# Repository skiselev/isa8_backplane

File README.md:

# ISA 8-bit Backplane
Compact ISA 8-bit Backplane board

## Introduction
This backplane was designed as a smaller version of [Micro ATX ISA Backplane](https://www.retrobrewcomputers.org/doku.php?id=boards:isa:isa-backplane:start). It can be used to build a compact IBM PC/XT compatible system using the [Micro 8088](https://github.com/skiselev/micro_8088)
processor board, and the 8-bit ISA cards that I've designed:
[ISA Super VGA](http://www.malinov.com/Home/sergeys-projects/isa-supervga),
[ISA Floppy Disk and Serial Controller](http://www.malinov.com/Home/sergeys-projects/isa-fdc-and-uart),
[XT-CF-Lite](http://www.malinov.com/Home/sergeys-projects/xt-cf-lite),
[ISA OPL2](http://www.malinov.com/Home/sergeys-projects/isa-opl2-card).

## Specifications
* 7 ISA 8-bit (62 pin) slots
* ATX power supply connector, and ATX power control circuit
* Bi-color activity LED, that changes the color when the processor is executing the code (the color changes every time A7 address line changes its value)
* The form factor is (mostly) compatible with ATX / Micro ATX
* Pads for optional termination resistors

## Hardware Documentation

### Schematic and PCB Layout

[Schematic - Version 1.0](KiCad/ISA8_Backplane-Schematic-1.0.pdf)

[PCB Layout - Version 1.0](KiCad/ISA8_Backplane-Board-1.0.pdf)

### Building Insturctions

Please refer to [Building Instructions](Building_Instructions.md) page for detailed instructions.

### Jumpers, Connectors, and Switches

#### P1 - ATX power connector
Pin | Description                    | Pin | Description
--- | ------------------------------ | --- | ------------------------------
1   | +3.3V power supply (not used)  | 11  | +3.3V power supply (not used)
2   |	+3.3V power supply (not used)  | 12  | -12V power supply
3   |	GND                            | 13  | Ground
4   |	+5V power supply               | 14  | Power supply ON signal
5   |	Ground                         | 15  | Ground
6   |	+5V power supply               | 16  | Ground
7   | Ground                         | 17  | Ground
8   | Power good (not used)          | 18  | -5V power supply (not used)*
9   | +5V standby power supply       | 19  | +5V power supply
10  | +12V power supply              | 20  | +5V power supply

*Note: -5V is not provided by most ATX power supplies. It is generated using an on board voltage regulator instead*

#### P2 - Power Switch connector
Pin | Description
--- | -----------
1   | Ground
2   |	Power ON signal

#### P3 - Power LED connector
Pin | Description
--- | -----------
1   | LED+
2   |	Ground

#### SW1 - Power Switch
Press SW1 to turn power on or off. The SW1 is connected in parallel with P2

### Bill of Materials - Version 1.0

[ISA 8-bit Backplane project on Mouser.com](https://www.mouser.com/ProjectManager/ProjectDetail.aspx?AccessID=9a09040b52) - View and order all components except of the PCB.

[ISA 8-bit Backplane project on OSH Park](https://oshpark.com/shared_projects/Y8dcyt5m) - View and order the PCB.

Component type     | Reference | Description                       | Quantity | Possible sources and notes 
------------------ | --------- | --------------------------------- | -------- | --------------------------
PCB                |           | ISA 8-bit Backplane PCB - Version 1.0  | 1   | Refer to the [RetroBrew Computers Board Inventory](https://retrobrewcomputers.org/doku.php?id=boardinventory#xi_8088_project_sergey_kiselev) page for ordering information, or order from a PCB manufacturer of your choice using provided Gerber or KiCad files
Integrated Circuit | U1        | 74HCT74, DIP-14 package           | 1        | Mouser [595-SN74AHCT74N](https://www.mouser.com/ProductDetail/595-SN74AHCT74N)
Integrated Circuit | U2        | 74HCT14, DIP-14 package           | 1        | Mouser [595-SN74AHCT14N](https://www.mouser.com/ProductDetail/595-SN74AHCT14N)
Integrated Circuit | U3        | LM7905C -5V voltage regulator     | 1        | Mouser [512-LM7905CT](https://www.mouser.com/ProductDetail/512-LM7905CT)
IC Socket          | U1, U2    | DIP-14, 300 mil socket            | 2        | Mouser [517-4814-3000-CP](https://www.mouser.com/ProductDetail/517-4814-3000-CP)
LED                | D1        | 3 mm, blue LED indicator          | 1        | Mouser [696-SSL-LX3054USBD](https://www.mouser.com/ProductDetail/696-SSL-LX3054USBD)
LED                | D2        | 3 mm, bi-color red/green LED indicator | 1   | Mouser [696-SSL-LX3054IGW](https://www.mouser.com/ProductDetail/696-SSL-LX3054IGW)
Diode              | D3, D4    | 1N4148                            | 2        | Mouser [512-1N4148](https://www.mouser.com/ProductDetail/512-1N4148)
Tactile Button     | SW1       | 6 mm tactile button, straight     | 1        | Mouser [653-B3F-1000](https://www.mouser.com/ProductDetail/653-B3F-1000)
Connector          | P1        | 20 pin ATX power connector        | 1        | Mouser [538-46015-2006](https://www.mouser.com/ProductDetail/538-46015-2006)
Connector          | P2, P3    | 4 pin header, 2.54 mm pitch       | 2        | Mouser [649-68002-104HLF](https://www.mouser.com/ProductDetail/649-68002-104HLF)
Connector          | BUS1-BUS7 | 62 pin card edge connector, 2.54 mm pitch | 7 | Mouser [571-6-5530843-5](https://www.mouser.com/ProductDetail/571-6-5530843-5)
Capacitor          | C1 - C19  | 10 uF, 16V, MLCC, 5 mm lead spacing    | 19       | Mouser [810-FG28X5R1E106MR06](https://www.mouser.com/ProductDetail/810-FG28X5R1E106MR06)
Capacitor          | C20       | 1 uF, MLCC, 5 mm lead spacing     | 1        | Mouser [810-FG28X5R1H105KRT0](https://www.mouser.com/ProductDetail/810-FG28X5R1H105KRT0)
Capacitor          | C21, C22  | 0.1 uF, MLCC, 5 mm lead spacing   | 2        | Mouser [594-K104K15X7RF53H5](https://www.mouser.com/ProductDetail/594-K104K15X7RF53H5)
Resistor           | R1, R2    | 10 kohm, through hole             | 2        | Mouser [291-10K-RC](https://www.mouser.com/ProductDetail/291-10K-RC)
Resistor           | R3        | 1 kohm, through hole              | 1        | Mouser [291-1K-RC](https://www.mouser.com/ProductDetail/291-1K-RC)
Resistor           | R4 - R7   | 470 ohm, through hole             | 4        | Mouser [291-470-RC](https://www.mouser.com/ProductDetail/291-470-RC)
Resistor Array     | RR1 - RR5 | do not populate                   |          | Optional, should not be populated

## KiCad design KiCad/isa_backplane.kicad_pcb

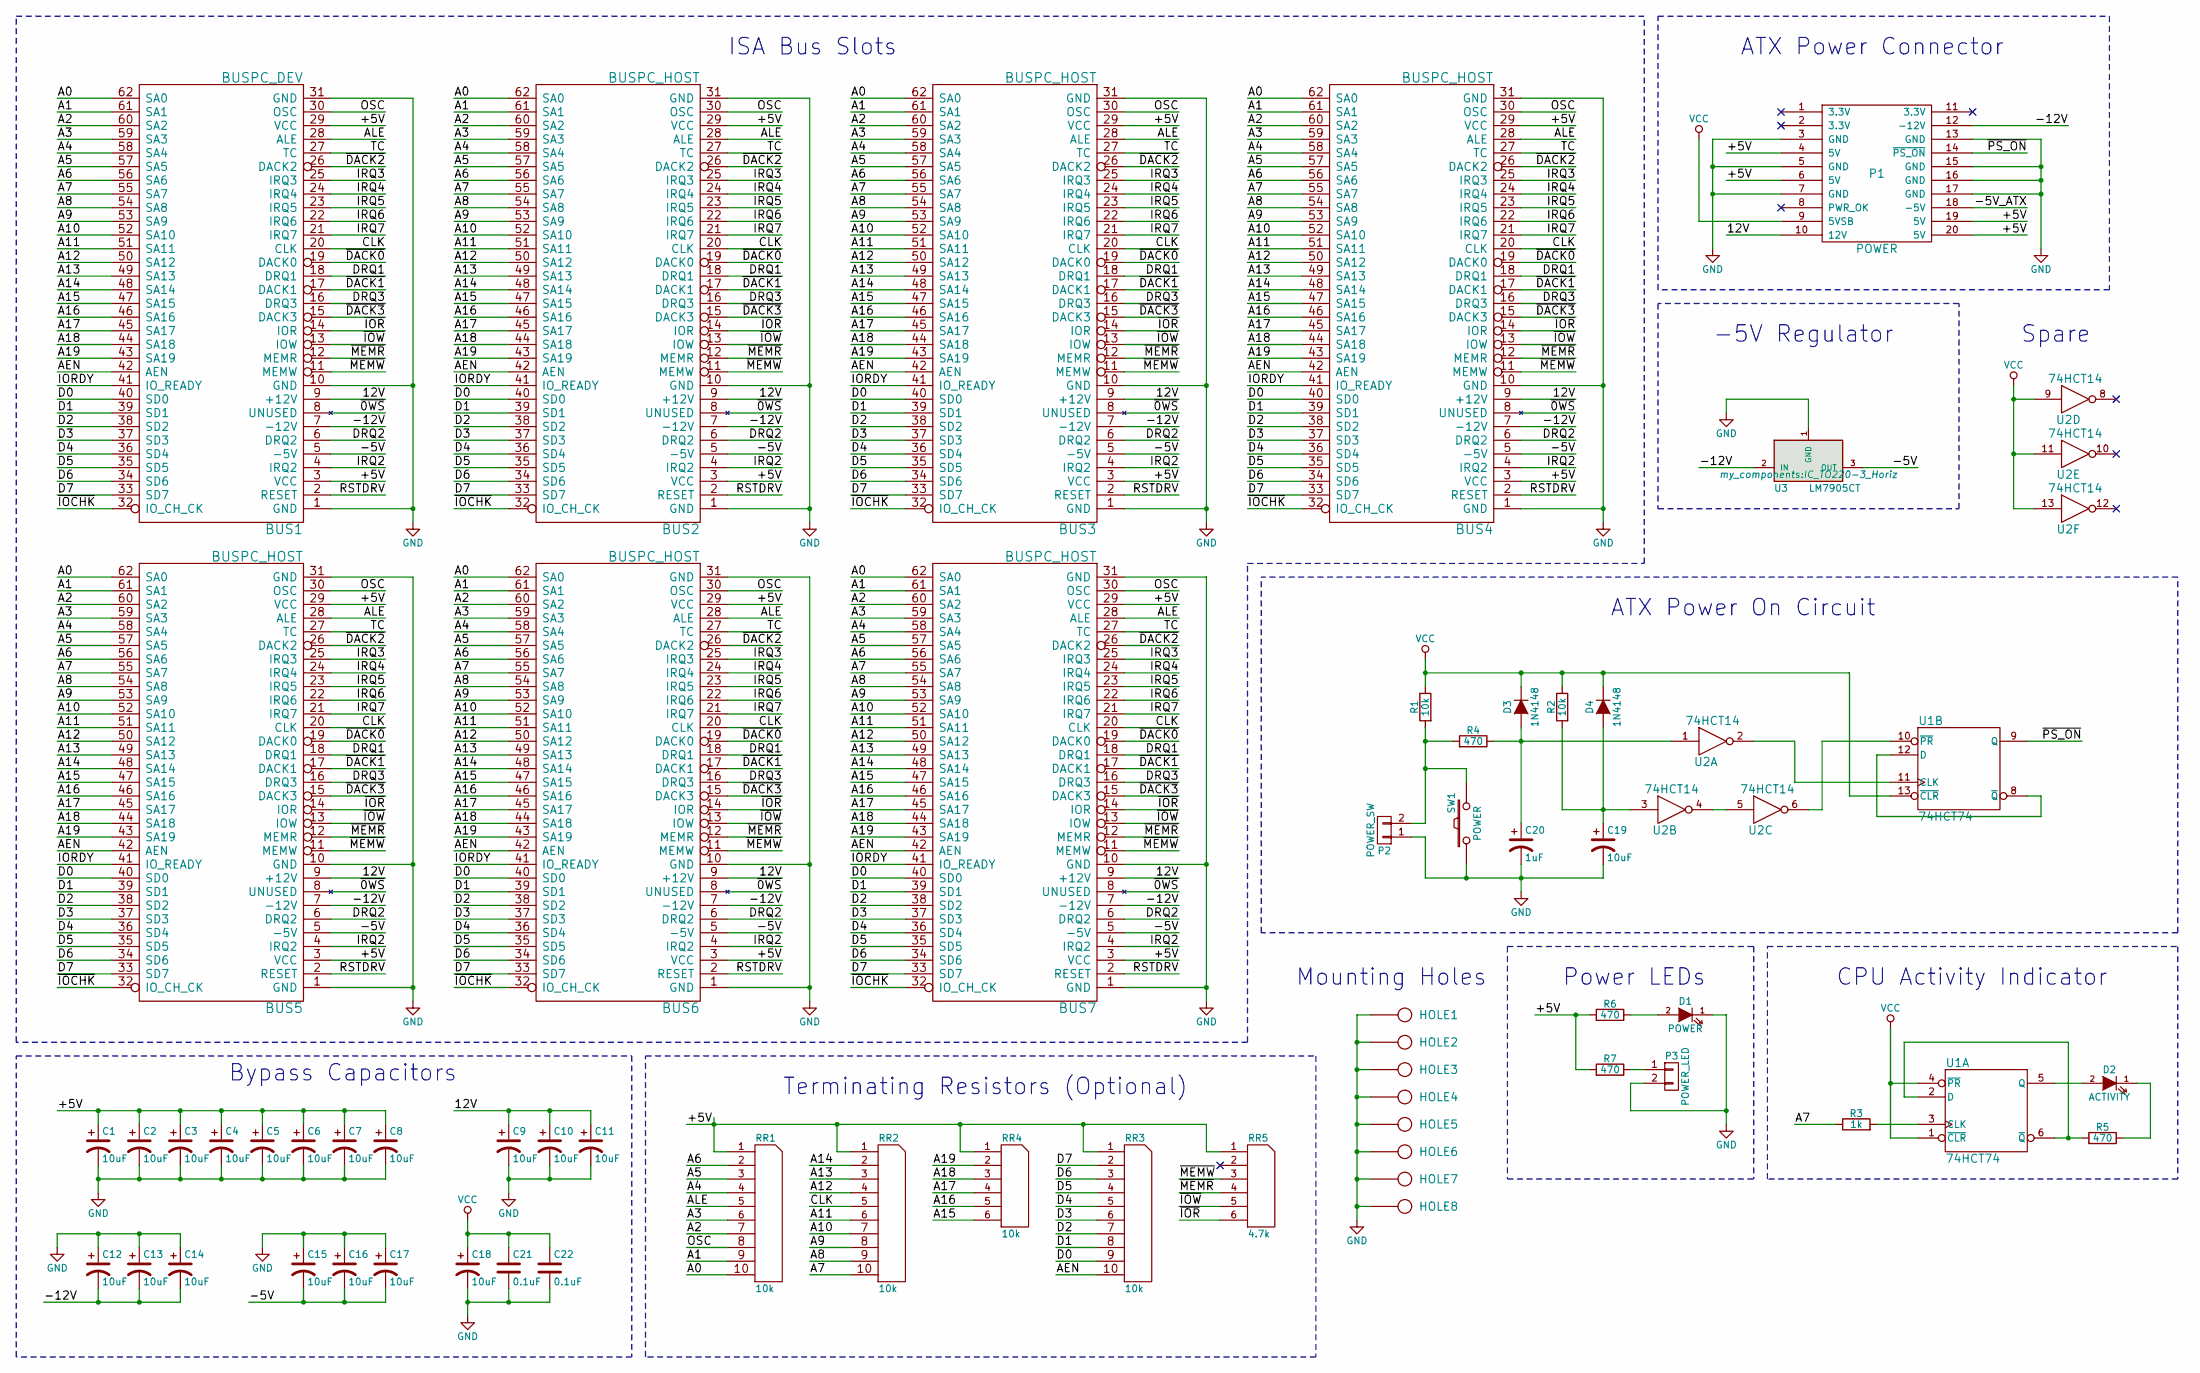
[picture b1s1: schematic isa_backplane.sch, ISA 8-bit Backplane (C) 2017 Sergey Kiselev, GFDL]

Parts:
BUS1: BUSPC_DEV; Conn_Edge_ISA8
BUS2, BUS3, BUS4, BUS5, BUS6, BUS7: BUSPC_HOST; Conn_Edge_ISA8
C1, C2, C3, C4, C5, C6, C7, C8, C9, C10, C11, C12, C13, C14, C15, C16, C17, C18, C19: 10uF; Cap_Tant_508
C20: 1uF; Cap_Tant_508
C21, C22: 0.1uF; Cap_Cer_508
D1: POWER; LED_3mm
D2: ACTIVITY; LED_3mm
D3, D4: 1N4148; Diode_762
HOLE1, HOLE2, HOLE3, HOLE4, HOLE5, HOLE6, HOLE7, HOLE8: HOLE; Hole_4mm
P1: POWER; Conn_Power_ATX_20pin
P2: POWER_SW; Conn_Pin_Header_2x1_2.54mm
P3: POWER_LED; Conn_Pin_Header_2x1_2.54mm
R1, R2: 10k; Res_762
R3: 1k; Res_762
R4, R5, R6, R7: 470; Res_762
RR1, RR2, RR3: 10k; Conn_SIL10
RR4: 10k; Conn_SIL6
RR5: 4.7k; Conn_SIL6
SW1: POWER; Switch_Tactile_6mm
U1: 74HCT74; IC_DIP14_300
U2: 74HCT14; IC_DIP14_300
U3: LM7905CT; IC_TO220-3_Horiz

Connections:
/12V: BUS1.9 (+12V), BUS2.9 (+12V), BUS3.9 (+12V), BUS4.9 (+12V), BUS5.9 (+12V), BUS6.9 (+12V), BUS7.9 (+12V), C9.1, C10.1, C11.1, P1.10 (12V)
/+5V: BUS1.3 (VCC), BUS1.29 (VCC), BUS2.3 (VCC), BUS2.29 (VCC), BUS3.3 (VCC), BUS3.29 (VCC), BUS4.3 (VCC), BUS4.29 (VCC), BUS5.3 (VCC), BUS5.29 (VCC), BUS6.3 (VCC), BUS6.29 (VCC), BUS7.3 (VCC), BUS7.29 (VCC), C1.1, C2.1, C3.1, C4.1, C5.1, C6.1, C7.1, C8.1, P1.4 (5V), P1.6 (5V), P1.19 (5V), P1.20 (5V), R6.2, R7.2, RR1.1 (COM), RR2.1 (COM), RR3.1 (COM), RR4.1 (COM), RR5.1 (COM)
/-5V: BUS1.5 (-5V), BUS2.5 (-5V), BUS3.5 (-5V), BUS4.5 (-5V), BUS5.5 (-5V), BUS6.5 (-5V), BUS7.5 (-5V), C15.2, C16.2, C17.2, U3.3 (OUT)
/-5V_ATX: P1.18 (-5V)
/-12V: BUS1.7 (-12V), BUS2.7 (-12V), BUS3.7 (-12V), BUS4.7 (-12V), BUS5.7 (-12V), BUS6.7 (-12V), BUS7.7 (-12V), C12.2, C13.2, C14.2, P1.12 (-12V), U3.2 (IN)
/A0: BUS1.62 (SA0), BUS2.62 (SA0), BUS3.62 (SA0), BUS4.62 (SA0), BUS5.62 (SA0), BUS6.62 (SA0), BUS7.62 (SA0), RR1.10
/A1: BUS1.61 (SA1), BUS2.61 (SA1), BUS3.61 (SA1), BUS4.61 (SA1), BUS5.61 (SA1), BUS6.61 (SA1), BUS7.61 (SA1), RR1.9
/A2: BUS1.60 (SA2), BUS2.60 (SA2), BUS3.60 (SA2), BUS4.60 (SA2), BUS5.60 (SA2), BUS6.60 (SA2), BUS7.60 (SA2), RR1.7
/A3: BUS1.59 (SA3), BUS2.59 (SA3), BUS3.59 (SA3), BUS4.59 (SA3), BUS5.59 (SA3), BUS6.59 (SA3), BUS7.59 (SA3), RR1.6
/A4: BUS1.58 (SA4), BUS2.58 (SA4), BUS3.58 (SA4), BUS4.58 (SA4), BUS5.58 (SA4), BUS6.58 (SA4), BUS7.58 (SA4), RR1.4
/A5: BUS1.57 (SA5), BUS2.57 (SA5), BUS3.57 (SA5), BUS4.57 (SA5), BUS5.57 (SA5), BUS6.57 (SA5), BUS7.57 (SA5), RR1.3
/A6: BUS1.56 (SA6), BUS2.56 (SA6), BUS3.56 (SA6), BUS4.56 (SA6), BUS5.56 (SA6), BUS6.56 (SA6), BUS7.56 (SA6), RR1.2
/A7: BUS1.55 (SA7), BUS2.55 (SA7), BUS3.55 (SA7), BUS4.55 (SA7), BUS5.55 (SA7), BUS6.55 (SA7), BUS7.55 (SA7), R3.1, RR2.10
/A8: BUS1.54 (SA8), BUS2.54 (SA8), BUS3.54 (SA8), BUS4.54 (SA8), BUS5.54 (SA8), BUS6.54 (SA8), BUS7.54 (SA8), RR2.9
/A9: BUS1.53 (SA9), BUS2.53 (SA9), BUS3.53 (SA9), BUS4.53 (SA9), BUS5.53 (SA9), BUS6.53 (SA9), BUS7.53 (SA9), RR2.8
/A10: BUS1.52 (SA10), BUS2.52 (SA10), BUS3.52 (SA10), BUS4.52 (SA10), BUS5.52 (SA10), BUS6.52 (SA10), BUS7.52 (SA10), RR2.7
/A11: BUS1.51 (SA11), BUS2.51 (SA11), BUS3.51 (SA11), BUS4.51 (SA11), BUS5.51 (SA11), BUS6.51 (SA11), BUS7.51 (SA11), RR2.6
/A12: BUS1.50 (SA12), BUS2.50 (SA12), BUS3.50 (SA12), BUS4.50 (SA12), BUS5.50 (SA12), BUS6.50 (SA12), BUS7.50 (SA12), RR2.4
/A13: BUS1.49 (SA13), BUS2.49 (SA13), BUS3.49 (SA13), BUS4.49 (SA13), BUS5.49 (SA13), BUS6.49 (SA13), BUS7.49 (SA13), RR2.3
/A14: BUS1.48 (SA14), BUS2.48 (SA14), BUS3.48 (SA14), BUS4.48 (SA14), BUS5.48 (SA14), BUS6.48 (SA14), BUS7.48 (SA14), RR2.2
/A15: BUS1.47 (SA15), BUS2.47 (SA15), BUS3.47 (SA15), BUS4.47 (SA15), BUS5.47 (SA15), BUS6.47 (SA15), BUS7.47 (SA15), RR4.6
/A16: BUS1.46 (SA16), BUS2.46 (SA16), BUS3.46 (SA16), BUS4.46 (SA16), BUS5.46 (SA16), BUS6.46 (SA16), BUS7.46 (SA16), RR4.5
/A17: BUS1.45 (SA17), BUS2.45 (SA17), BUS3.45 (SA17), BUS4.45 (SA17), BUS5.45 (SA17), BUS6.45 (SA17), BUS7.45 (SA17), RR4.4
/A18: BUS1.44 (SA18), BUS2.44 (SA18), BUS3.44 (SA18), BUS4.44 (SA18), BUS5.44 (SA18), BUS6.44 (SA18), BUS7.44 (SA18), RR4.3
/A19: BUS1.43 (SA19), BUS2.43 (SA19), BUS3.43 (SA19), BUS4.43 (SA19), BUS5.43 (SA19), BUS6.43 (SA19), BUS7.43 (SA19), RR4.2
/AEN: BUS1.42 (AEN), BUS2.42 (AEN), BUS3.42 (AEN), BUS4.42 (AEN), BUS5.42 (AEN), BUS6.42 (AEN), BUS7.42 (AEN), RR3.10
/ALE: BUS1.28 (ALE), BUS2.28 (ALE), BUS3.28 (ALE), BUS4.28 (ALE), BUS5.28 (ALE), BUS6.28 (ALE), BUS7.28 (ALE), RR1.5
/CLK: BUS1.20 (CLK), BUS2.20 (CLK), BUS3.20 (CLK), BUS4.20 (CLK), BUS5.20 (CLK), BUS6.20 (CLK), BUS7.20 (CLK), RR2.5
/D0: BUS1.40 (SD0), BUS2.40 (SD0), BUS3.40 (SD0), BUS4.40 (SD0), BUS5.40 (SD0), BUS6.40 (SD0), BUS7.40 (SD0), RR3.9
/D1: BUS1.39 (SD1), BUS2.39 (SD1), BUS3.39 (SD1), BUS4.39 (SD1), BUS5.39 (SD1), BUS6.39 (SD1), BUS7.39 (SD1), RR3.8
/D2: BUS1.38 (SD2), BUS2.38 (SD2), BUS3.38 (SD2), BUS4.38 (SD2), BUS5.38 (SD2), BUS6.38 (SD2), BUS7.38 (SD2), RR3.7
/D3: BUS1.37 (SD3), BUS2.37 (SD3), BUS3.37 (SD3), BUS4.37 (SD3), BUS5.37 (SD3), BUS6.37 (SD3), BUS7.37 (SD3), RR3.6
/D4: BUS1.36 (SD4), BUS2.36 (SD4), BUS3.36 (SD4), BUS4.36 (SD4), BUS5.36 (SD4), BUS6.36 (SD4), BUS7.36 (SD4), RR3.5
/D5: BUS1.35 (SD5), BUS2.35 (SD5), BUS3.35 (SD5), BUS4.35 (SD5), BUS5.35 (SD5), BUS6.35 (SD5), BUS7.35 (SD5), RR3.4
/D6: BUS1.34 (SD6), BUS2.34 (SD6), BUS3.34 (SD6), BUS4.34 (SD6), BUS5.34 (SD6), BUS6.34 (SD6), BUS7.34 (SD6), RR3.3
/D7: BUS1.33 (SD7), BUS2.33 (SD7), BUS3.33 (SD7), BUS4.33 (SD7), BUS5.33 (SD7), BUS6.33 (SD7), BUS7.33 (SD7), RR3.2
/DRQ1: BUS1.18 (DRQ1), BUS2.18 (DRQ1), BUS3.18 (DRQ1), BUS4.18 (DRQ1), BUS5.18 (DRQ1), BUS6.18 (DRQ1), BUS7.18 (DRQ1)
/DRQ2: BUS1.6 (DRQ2), BUS2.6 (DRQ2), BUS3.6 (DRQ2), BUS4.6 (DRQ2), BUS5.6 (DRQ2), BUS6.6 (DRQ2), BUS7.6 (DRQ2)
/DRQ3: BUS1.16 (DRQ3), BUS2.16 (DRQ3), BUS3.16 (DRQ3), BUS4.16 (DRQ3), BUS5.16 (DRQ3), BUS6.16 (DRQ3), BUS7.16 (DRQ3)
/IORDY: BUS1.41 (IO_READY), BUS2.41 (IO_READY), BUS3.41 (IO_READY), BUS4.41 (IO_READY), BUS5.41 (IO_READY), BUS6.41 (IO_READY), BUS7.41 (IO_READY)
/IRQ2: BUS1.4 (IRQ2), BUS2.4 (IRQ2), BUS3.4 (IRQ2), BUS4.4 (IRQ2), BUS5.4 (IRQ2), BUS6.4 (IRQ2), BUS7.4 (IRQ2)
/IRQ3: BUS1.25 (IRQ3), BUS2.25 (IRQ3), BUS3.25 (IRQ3), BUS4.25 (IRQ3), BUS5.25 (IRQ3), BUS6.25 (IRQ3), BUS7.25 (IRQ3)
/IRQ4: BUS1.24 (IRQ4), BUS2.24 (IRQ4), BUS3.24 (IRQ4), BUS4.24 (IRQ4), BUS5.24 (IRQ4), BUS6.24 (IRQ4), BUS7.24 (IRQ4)
/IRQ5: BUS1.23 (IRQ5), BUS2.23 (IRQ5), BUS3.23 (IRQ5), BUS4.23 (IRQ5), BUS5.23 (IRQ5), BUS6.23 (IRQ5), BUS7.23 (IRQ5)
/IRQ6: BUS1.22 (IRQ6), BUS2.22 (IRQ6), BUS3.22 (IRQ6), BUS4.22 (IRQ6), BUS5.22 (IRQ6), BUS6.22 (IRQ6), BUS7.22 (IRQ6)
/IRQ7: BUS1.21 (IRQ7), BUS2.21 (IRQ7), BUS3.21 (IRQ7), BUS4.21 (IRQ7), BUS5.21 (IRQ7), BUS6.21 (IRQ7), BUS7.21 (IRQ7)
/OSC: BUS1.30 (OSC), BUS2.30 (OSC), BUS3.30 (OSC), BUS4.30 (OSC), BUS5.30 (OSC), BUS6.30 (OSC), BUS7.30 (OSC), RR1.8
/RSTDRV: BUS1.2 (RESET), BUS2.2 (RESET), BUS3.2 (RESET), BUS4.2 (RESET), BUS5.2 (RESET), BUS6.2 (RESET), BUS7.2 (RESET)
/TC: BUS1.27 (TC), BUS2.27 (TC), BUS3.27 (TC), BUS4.27 (TC), BUS5.27 (TC), BUS6.27 (TC), BUS7.27 (TC)
/~0WS: BUS1.8 (UNUSED), BUS2.8 (UNUSED), BUS3.8 (UNUSED), BUS4.8 (UNUSED), BUS5.8 (UNUSED), BUS6.8 (UNUSED), BUS7.8 (UNUSED)
/~DACK0: BUS1.19 (DACK0), BUS2.19 (DACK0), BUS3.19 (DACK0), BUS4.19 (DACK0), BUS5.19 (DACK0), BUS6.19 (DACK0), BUS7.19 (DACK0)
/~DACK1: BUS1.17 (DACK1), BUS2.17 (DACK1), BUS3.17 (DACK1), BUS4.17 (DACK1), BUS5.17 (DACK1), BUS6.17 (DACK1), BUS7.17 (DACK1)
/~DACK2: BUS1.26 (DACK2), BUS2.26 (DACK2), BUS3.26 (DACK2), BUS4.26 (DACK2), BUS5.26 (DACK2), BUS6.26 (DACK2), BUS7.26 (DACK2)
/~DACK3: BUS1.15 (DACK3), BUS2.15 (DACK3), BUS3.15 (DACK3), BUS4.15 (DACK3), BUS5.15 (DACK3), BUS6.15 (DACK3), BUS7.15 (DACK3)
/~IOCHK: BUS1.32 (IO_CH_CK), BUS2.32 (IO_CH_CK), BUS3.32 (IO_CH_CK), BUS4.32 (IO_CH_CK), BUS5.32 (IO_CH_CK), BUS6.32 (IO_CH_CK), BUS7.32 (IO_CH_CK)
/~IOR: BUS1.14 (IOR), BUS2.14 (IOR), BUS3.14 (IOR), BUS4.14 (IOR), BUS5.14 (IOR), BUS6.14 (IOR), BUS7.14 (IOR), RR5.6
/~IOW: BUS1.13 (IOW), BUS2.13 (IOW), BUS3.13 (IOW), BUS4.13 (IOW), BUS5.13 (IOW), BUS6.13 (IOW), BUS7.13 (IOW), RR5.5
/~MEMR: BUS1.12 (MEMR), BUS2.12 (MEMR), BUS3.12 (MEMR), BUS4.12 (MEMR), BUS5.12 (MEMR), BUS6.12 (MEMR), BUS7.12 (MEMR), RR5.4
/~MEMW: BUS1.11 (MEMW), BUS2.11 (MEMW), BUS3.11 (MEMW), BUS4.11 (MEMW), BUS5.11 (MEMW), BUS6.11 (MEMW), BUS7.11 (MEMW), RR5.3
/~PS_ON: P1.14 (~PS_ON), U1.9 (Q)
GND: BUS1.1 (GND), BUS1.10 (GND), BUS1.31 (GND), BUS2.1 (GND), BUS2.10 (GND), BUS2.31 (GND), BUS3.1 (GND), BUS3.10 (GND), BUS3.31 (GND), BUS4.1 (GND), BUS4.10 (GND), BUS4.31 (GND), BUS5.1 (GND), BUS5.10 (GND), BUS5.31 (GND), BUS6.1 (GND), BUS6.10 (GND), BUS6.31 (GND), BUS7.1 (GND), BUS7.10 (GND), BUS7.31 (GND), C1.2, C2.2, C3.2, C4.2, C5.2, C6.2, C7.2, C8.2, C9.2, C10.2, C11.2, C12.1, C13.1, C14.1, C15.1, C16.1, C17.1, C18.2, C19.2, C20.2, C21.2, C22.2, D1.1 (K), HOLE1.1, HOLE2.1, HOLE3.1, HOLE4.1, HOLE5.1, HOLE6.1, HOLE7.1, HOLE8.1, P1.3 (GND), P1.5 (GND), P1.7 (GND), P1.13 (GND), P1.15 (GND), P1.16 (GND), P1.17 (GND), P2.1, P3.2, SW1.1, U1.7 (GND), U2.7 (GND), U3.1 (GND)
unnamed: C19.1, D4.2 (A), R2.2, U2.3
unnamed: C20.1, D3.2 (A), R4.1, U2.1
unnamed: D1.2 (A), R6.1
unnamed: D2.1 (K), R5.1
unnamed: D2.2 (A), U1.5 (Q)
unnamed: P2.2, R1.2, R4.2, SW1.2
unnamed: P3.1, R7.1
unnamed: R3.2, U1.3 (CLK)
unnamed: R5.2, U1.2 (D), U1.6 (~Q)
unnamed: U1.10 (~PR), U2.6
unnamed: U1.11 (CLK), U2.2
unnamed: U1.8 (~Q), U1.12 (D)
unnamed: U2.4, U2.5
VCC: C18.1, C21.1, C22.1, D3.1 (K), D4.1 (K), P1.9 (5VSB), R1.1, R2.1, U1.1 (~CLR), U1.4 (~PR), U1.13 (~CLR), U1.14 (VCC), U2.9, U2.11, U2.13, U2.14 (VCC)

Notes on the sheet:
Power LEDs
-5V Regulator
CPU Activity Indicator
ATX Power Connector
Mounting Holes
ATX Power On Circuit
Bypass Capacitors
ISA Bus Slots
Terminating Resistors (Optional)
Spare

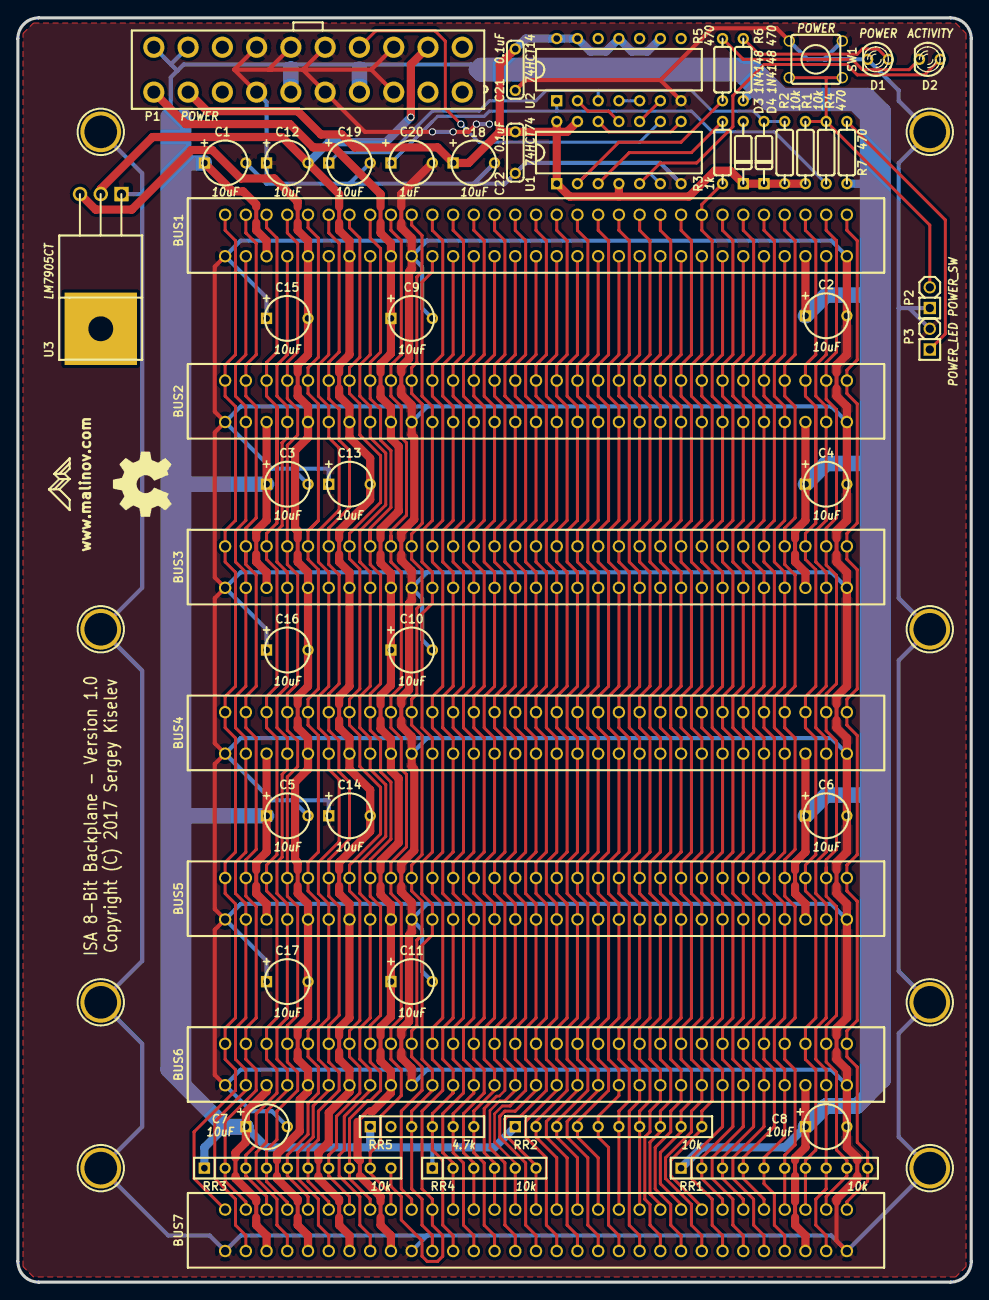
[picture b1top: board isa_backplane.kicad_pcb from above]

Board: 2 copper layers, 116.8 x 154.9 mm, 60 parts (0 on the bottom side), 74 nets.

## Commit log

2018-01-06 add the files
2018-01-06 add board picture
2018-01-06 README.md: Initial version
2018-01-06 README.md: Add board photo
2018-01-06 README.md: Update BOM
2018-01-06 README.md: Update LM7905 reference
2018-01-06 Building_Instructions.md: Initial content
2018-01-09 README.md: Update C1-C19 type - needs to be >= 16V
2018-10-17 Remove mention of the Faraday
    There is no such component on this backplane. I suppose this is the result of a copy/paste from another project.
2020-04-02 README: Update the quantity of 470 ohm resistors

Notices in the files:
KiCad/isa_backplane.kicad_pcb:
Copyright (C) 2017 Sergey Kiselev
